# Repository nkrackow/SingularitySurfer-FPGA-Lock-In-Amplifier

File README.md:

# SingularitySurfer: An FPGA Lock-In Amplifier
Repository of an FPGA based DSP Lock-In Amplifier.

## Fotos:

Measuring the change of phase due to changing the distance of two speakers (of which one functions as a crappy microphone):

## Block Diagram:

## Overview:
Lock-In amplifiers are a very useful tool in many physics and bio experiments where your signal of interest might be covered by a lot of noise and interference. It does so by effectively correlating out the signal of interest. As analog components are always subject to noise, drift and non-linearities, performance in a DSP Lock-In can be far superior.
The project leverages the affordable ICE40 FPGA with its fully open source toolchain to implement the digital signal processing. Analog components are implemented in a manner that strikes a balance between performance and cost. As the analog frontend mostly determines the overall performance, a focus was put on its implementation. The total BOM cost is below 70€.
The SingularitySurfer was developed as a personal learning platform that I share so others can get design ideas and see my approach. It does not intend to give reference designs or to teach the subject. 
Cores from other people:
* CORDIC: https://opencores.org/projects/verilog_cordic_core
* SPI flash reader: https://github.com/smunaut/ice40-playground/tree/master/cores/spi_flash
* 2x16 character display driver: https://opencores.org/projects/wb_lcd

The next sections will describe the features of the various sub-systems, their development and the design decisions made.

## Digital architecture:
All of the FPGA cores run at a 36MHz base clock and the numeric oscillator, DDS, PLL and DACs also run at this sample frequency. However the ADC samples at 900kHz and the digital filters further downsample the signal by a factor of 1024. The DDS and the ADC produce signed 16 bit signals, while the output of the multipliers and filters are signed 32 bit. The phase signals from the PLL and oscillator are 18 bit. Due to FPGA LUT constraints, the CORDIC core only uses signed 16bit precision and the algorithm is terminated after 9 iterations. Most of the cores, especially the CORDIC core, make use of pipelining to maintain the 36MHz clock. The full design takes up about 85% of the FPGA LUTs.

## FPGA:
The Lattice ICE40UP5K is an ideal platform for a small DSP project like this. It offers:
* sufficient LUTs for all of the wiring, UI, display and housekeeping
* 8 16x16 hardware multipliers for signal processing
* 1Mbit of internal SRAM for storing a high fidelity sine lookup table
* QFP package which is easily soldered by hand
* affordable price at just 5€
* fully open source toolchain!

## Analog frontend:
As all of the digital signal processing is deterministic and can be upgraded at a later point, the Lock-In’s performance is ultimately determined by the analog frontend. The goal is to transfer the signal into the digital domain with little disturbance. This requires high dynamic range, low noise and high linearity. But as cost was also a factor in the development, compromises had to be made. The design employs:
* ADC: MCP33131D, 1MSps, 16bit, 91.3dB SNR 
* Voltage reference: REF5050, low noise, low drift
* PGA: AD8253, 0-60dB gain, low distortion, low noise, instrumentation amplifier
* OpAmp: AD8675, low noise
* Voltage regulator: LT3032-15, dual +-15V, low noise

At the input there is a 100kHz RC lowpass and the ADC AA filter is tuned to 100kHz as well. The PGA doubles as the ADC driver, using the AD8675 to make the signal differential. This setup was used to cut the cost of a dedicated ADC driver. Unfortunately it does limit performance, as it does introduce some distortion due to the PGA output not being fast enough to drive the ADC (which is not critical as distortion is essentially the same as noise well outside the passband of the digital lowpass). Broadband noise from the analog components was below the quantization noise and therefore not visible at the ADC output.

## DDS and numeric oscillator:
The direct digital synthesis core generates a digital representation of a sinusoidal using a 1/4 sinus look-up table stored in the 1Mbit SRAM. The other 3/4 of the sine and the cosine can be easily generated from the first 1/4 using symmetries. Therefore a high fidelity, 16bit amplitude, 18bit phase representation of the sinusoidals can be generated. When using an external reference signal, the DDS uses the phase of the digital PLL locked to the external reference signal. When generating its own reference signal, a numeric oscillator with an internal 32bit phase accumulator is employed. 
In order to avoid spurious tones in the output spectrum of the DDS when using the internal oscillator, dithering of the last phase-bit is applied using a linear-feedback shift register. Unfortunately the ICE40 SRAM blocks don't support initial values in the FPGA bitstream. Therefore the look-up table is permanently stored in the external SPI flash and loaded into SRAM after every startup.

## DAC:
As the Lock-In’s performance is not dependent on the output reference signal (as long as it contains a strong spectral component exactly at the reference frequency and other spectral components are masked by the noise added in the DUT), a basic sigma-delta DAC is used. Same goes for the X/R and Y/Theta "baseband" outputs, as they are essentially just DC (however DC accuracy has to be considered here) . The sigma-delta DACs require just a single FPGA pin and a passive second order lowpass with buffered output as external hardware in order to generate analog signals. Inside the FPGA the DAC uses a basic first-order sigma-delta modulator. With a modulator frequency of 36 MHz and 100kHz lowpass cutoff, the SNR is still better than 60dB. However switching many single-ended FPGA pins at these frequencies might lead to high EMI emissions. This was tried to be avoided by placing the lowpass filter close to the FPGA pins.

## PLL *(experimental)*:
The all-digital PLL gets a clean digital input signal by the use of a Schmitt-Trigger at the reference input. It uses a 32bit phase accumulator and 17bit phase increment word which leads to good phase precision. The DP controller can update the phase increment word without the need for multipliers by simply bit shifting the error signals. The controller can therefore only be tuned very coarsely which was done by simple trial and error. With this setup the controller can lock and track any reference signal between 500Hz and 100kHz. However it can get stuck in "limbo" with an aperiodic input signal and needs a reset to recover.

## Multipliers and CIC filter:
Twor 16x16 hardware multipliers directly "mix" the incoming ADC samples with the sine/cosine signals from the DDS core. The output is therefore a 32bit signal at ADC sampling speed. 
This signal needs to be lowpass filtered to get rid of the undesired mixing products, ideally with a very low cutoff frequency (i.e. long time-constant). At ADC sampling speed this would require a lot of memory. But as the desired signal is bandlimited to a very low frequency (10s or 100s of Hz), a high sampling rate is unnecessary. A cascaded integrator comb (CIC) filter can downsample and lowpass filter the signal at the same time. Furthermore the cutoff frequency can easily be changed in powers of two and it doesn’t require hardware multipliers. 
The downside is that the frequency response is far from an ideal lowpass. Fortunately in the case of the lock-in, this is not critical, as the cutoff frequencies are so low and the upper mixer output products are far higher than fc (it will just let more noise through which can be counteracted by a longer filter time constant). In fact right now, only a single IC stage is used in the SingularitySurfer, as there is already not enough memory for a second integrator. A good improvement would be to follow the CIC with an IIR filter using the remaining hardware multipliers.

## *(update 2020)* Multiplier less IIR filter
The SingularitySurfer was recently upgraded with a better lowpass using a very clever first order IIR filter. It uses the fact that you can multiply by a number close to 1 with bitshifting in hardware. E.g x*(15/16) can be accomplished via x-(x>>4). See [PYTHON_FILTER](https://github.com/SingularitySurfer/SingularitySurfer-FPGA-Lock-In-Amplifier/tree/master/PYTHON_FILTER) for a python demonstration.

## CORDIC:
The CORDIC algorithm computes the angle and magnitude of the sine and cosine signals. The original core by Dale Dickard was extended to support full 360 degree rotation and modified to fit into the remaining ICE40 logic. 

## Display and UI:
The display allows direct monitoring of the Lock-In outputs and user interaction with the UI. The UI is controlled via four buttons on the side of the display. This way the user can navigate through the device settings:
* Filter time constant: between 2^0 and 2^15 milliseconds
* PGA gain: 0dB, 20dB, 40dB, 60dB
* Internal/external reference 
* Internal reference frequency: 500Hz, 1kHz, 2kHz, 5kHz, 10kHz, 20kHz, 50 kHz, 100kHz
*  Internal reference output amplitude: 0.45V, 0.9V, 1.6V, 3.3V (peak to peak)

The signal monitoring can easily be switched between X/Y and R/θ view. The display is a simple 2x16 character LCD display with built-in character ROM. Unfortunately, the maximum update rate of such a display is about 2Hz. A higher update rate would lead to a more direct user feedback when monitoring signals. The logic to drive the display, show text, decimal numbers, etc., is actually not trivial and a small embedded processor could be a better idea in a future project.

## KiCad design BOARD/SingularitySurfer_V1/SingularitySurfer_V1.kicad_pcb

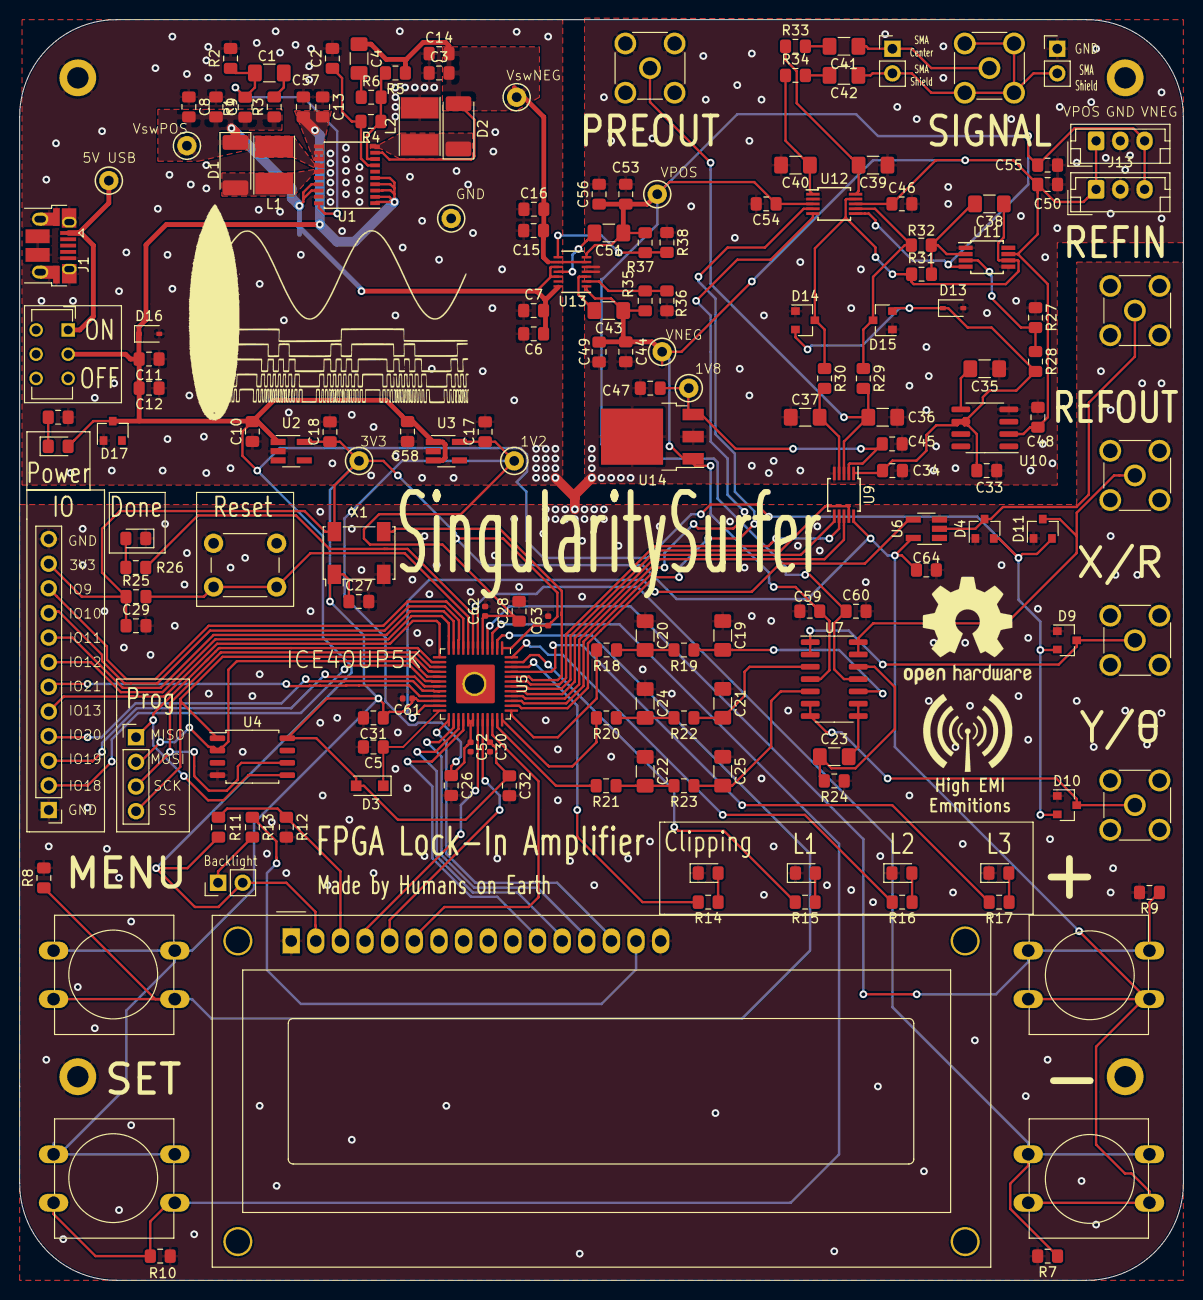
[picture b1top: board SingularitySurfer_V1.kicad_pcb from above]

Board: 2 copper layers, 120.0 x 130.0 mm, 171 parts (0 on the bottom side), 99 nets.

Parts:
 : TestPoint; TestPoint_Keystone_5000-5004_Miniature
 #2,  #3,  #4,  #5: MountingHole_2.2mm_M2_DIN965_Pad
 #6: Conn_01x02_Male; PinHeader_1x02_P2.54mm_Vertical
 #7: Conn_01x12; PinHeader_1x12_P2.54mm_Vertical
 #8: Conn_01x04_Male; PinHeader_1x04_P2.54mm_Vertical
 #9,  #12,  #13,  #14,  #15,  #16,  #17,  #18: TestPoint; TestPoint_Keystone_5000-5004_Miniature
 #10: R; R_0805_2012Metric_Pad1.15x1.40mm_HandSolder
 #11: Conn_01x03; JST_EH_B3B-EH-A_1x03_P2.50mm_Vertical
 #19,  #20,  #21,  #22,  #23,  #24: LED; LED_0805_2012Metric_Pad1.15x1.40mm_HandSolder
 #25,  #27,  #30,  #31,  #32,  #33: Conn_Coaxial; SMA_Molex_73251-2200_Horizontal
 #26: SW_Push; SW_PUSH_6mm
 #28,  #29: Conn_01x02; PinHeader_1x02_P2.54mm_Vertical
 #34: WC1602A
 #35: SW_DIP_x01; SW_CuK_JS202011AQN_DPDT_Angled
+1: SW_Push; SW_PUSH-12mm
-1: SW_Push; SW_PUSH-12mm
C1, C4, C19, C20, C21, C22, C23, C24, C25, C36, C37, C38, C39, C40, C41, C42, C43, C51: C; C_1206_3216Metric_Pad1.42x1.75mm_HandSolder
C2, C3, C5, C6, C7, C8, C9, C10, C11, C12, C13, C14, C15, C16, C17, C18, C26, C27, C28, C29, C31, C32, C44, C45, C46, C47, C48, C49, C50, C53, C54, C55, C56, C57, C58, C59, C60, C64: C; C_0805_2012Metric_Pad1.15x1.40mm_HandSolder
C30, C52, C61, C62, C63: C; C_0402_1005Metric
C33, C34: 10u; C_0805_2012Metric_Pad1.15x1.40mm_HandSolder
C35: 1u; C_1206_3216Metric_Pad1.42x1.75mm_HandSolder
D1, D2: D; D_2010_5025Metric_Pad1.52x2.65mm_HandSolder
D3: D; D_SOD-123F
D4, D9, D10, D11, D14, D15, D17: D_Schottky_x2_Serial_AKC; SOT-23
D13, D16: D_Zener; D_SOD-323
J1: USB_B_Micro; USB_Micro-B_Amphenol_10103594-0001LF_Horizontal
J13: Conn_01x03; JST_EH_B3B-EH-A_1x03_P2.50mm_Vertical
L1, L2: INDUCTOR; L_Taiyo-Yuden_NR-40xx_HandSoldering
MENU1: SW_Push; SW_PUSH-12mm
R1, R2, R3, R4, R5, R6, R7, R8, R9, R10, R11, R12, R13, R14, R15, R16, R17, R18, R19, R20, R21, R22, R23, R24, R25, R26, R27, R28, R29, R30, R31, R32, R33, R34, R35, R36, R37, R38: R; R_0805_2012Metric_Pad1.15x1.40mm_HandSolder
SET1: SW_Push; SW_PUSH-12mm
U1: BD81870EFV; SSOP-20_4.4x6.5mm_P0.65mm
U2: MIC5504-3.3YM5; SOT-23-5_HandSoldering
U3: TLV70212_SOT23-5; SOT-23-5_HandSoldering
U4: W25Q32JVSS; SOIC-8_5.23x5.23mm_P1.27mm
U5: ICE40UP5K-SG48ITR; QFN-48-1EP_7x7mm_P0.5mm_EP5.6x5.6mm
U6: 74LVC1G17; SOT-23-5_HandSoldering
U7: OPA1679; SOIC-14_3.9x8.7mm_P1.27mm
U9: MCP33131D; MSOP-10_3x3mm_P0.5mm
U10: REF5050AD; SOIC-8_3.9x4.9mm_P1.27mm
U11: AD8675; MSOP-8_3x3mm_P0.65mm
U12: AD8253; MSOP-10_3x3mm_P0.5mm
U13: LT3032; DFN-14-1EP_split_bottom_pad_3x4mm_P0.5mm_EP1.7x3.3mm
U14: AP2114-1.8; TO-252-3_TabPin2
X1: DFA-S11; Oscillator_SMD_Fordahl_DFAS11-4Pin_7.0x5.0mm

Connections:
1V2: #12.1, C17.1, C26.1, C28.1, C52.1, C62.1, U3.5, U5.5, U5.29, U5.30
1V8: #16.1, C45.1, C47.1, U9.2, U14.3
3V3: #7.11, #9.1, +1.2, -1.2, C18.1, C27.1, C29.1, C30.1, C31.1, C32.1, C61.1, C63.1, C64.1, D3.2, MENU1.2, R25.1, SET1.2, U2.5, U4.8, U5.1, U5.22, U5.33, U6.5, U9.10, X1.1, X1.4
5V: #6.2, #19.2, #34.2, #35.2, C10.2, C11.2, C12.2, C13.2, C57.2, C58.2, D4.2, D9.2, D10.2, D11.2, D16.1, D17.3, R11.1, U1.1, U1.2, U1.3, U1.4, U1.5, U1.11, U1.12, U1.13, U2.1, U3.1, U3.3
+8V: #11.1, #15.1, C43.1, C44.1, C46.1, C48.1, C49.1, C50.1, C59.1, J13.1, R35.2, U7.4, U10.2, U11.7, U12.8, U13.1, U14.1
-8V: #11.3, #13.1, C51.1, C53.1, C54.1, C55.1, C56.1, C60.1, J13.3, R37.2, U7.11, U11.4, U12.3, U12.6, U13.7
/Power/VNEG: #14.1, C3.2, C4.1, C14.2, C15.2, C16.2, D2.2, R5.1, U1.9, U13.6, U13.9
A0: U5.38, U12.4
A1: U5.39, U12.5
CDONE: R26.2, U5.7
CONVST: U5.41, U9.6
GND: .1, #2.1, #3.1, #4.1, #5.1, #7.1, #7.12, #10.1, #11.2, #20.1, #21.1, #22.1, #23.1, #24.1, #25.2, #26.1, #28.1, #30.2, #31.2, #32.2, #33.2, #34.1, #34.16, C2.2, C3.1, C5.2, C6.1, C7.1, C8.1, C9.1, C10.1, C11.1, C12.1, C13.1, C14.1, C15.1, C16.1, C17.2, C18.2, C19.1, C20.1, C21.1, C22.1, C24.1, C25.1, C26.2, C27.2, C28.2, C29.2, C30.2, C31.2, C32.2, C33.2, C34.2, C35.1, C36.1, C37.1, C39.1, C40.2, C44.2, C45.2, C46.2, C47.2, C48.2, C49.2, C50.2, C52.2, C53.2, C54.2, C55.2, C56.2, C57.1, C58.1, C59.2, C60.2, C61.2, C62.2, C63.2, C64.2, D4.1, D9.1, D10.1, D11.1, D13.2, D14.1, D15.1, D16.2, D17.1, J1.5, J1.6, J13.2, L2.2, R2.2, R7.2, R8.2, R9.2, R10.2, R12.2, R24.1, R27.1, R36.1, R38.1, U1.16, U1.19, U2.2, U3.2, U4.4, U5.49, U6.3, U9.5, U10.4, U11.1, U11.5, U12.2, U13.4, U13.5, U14.2, X1.2
unnamed: +1.1, R9.1, U5.4
unnamed: -1.1, R7.1, U5.6
unnamed: C1.1, R3.2
unnamed: C1.2, R1.2, R2.1, U1.20
unnamed: C2.1, R4.2, U1.7
unnamed: C4.2, R6.1
unnamed: C5.1, D3.1, U5.24
unnamed: C19.2, R19.1, U7.10
unnamed: C20.2, R18.1, R19.2
unnamed: C21.2, R22.1, U7.3
unnamed: C22.2, R21.1, R23.2
unnamed: C23.1, R24.2, U7.12
unnamed: C23.2, U7.8, U7.9
unnamed: C24.2, R20.1, R22.2
unnamed: C25.2, R23.1, U7.5
unnamed: C33.1, C34.1, D13.1, D14.2, D15.2, R28.2, U9.1, U10.6
unnamed: C35.2, U10.5
unnamed: #25.1, C36.2, R29.2, U9.3
unnamed: C37.2, R30.2, U9.4
unnamed: C38.1, D14.3, R30.1, R31.1, U11.6, U12.9
unnamed: C38.2, R31.2, R32.2, U11.2
unnamed: C39.2, R33.1, U12.10
unnamed: C40.1, R34.1, U12.1
unnamed: #27.1, #29.1, C41.1
unnamed: C41.2, R33.2
unnamed: #27.2, #28.2, #29.2, C42.1
unnamed: C42.2, R34.2
unnamed: C43.2, U13.3
unnamed: C51.2, U13.11
unnamed: D1.2, L1.1, U1.15
unnamed: D2.1, L2.1, U1.10
unnamed: #33.1, D4.3, U6.2
unnamed: #24.2, R14.1
unnamed: #23.2, R15.1
unnamed: #22.2, R16.1
unnamed: #21.2, R17.1
unnamed: #31.1, D9.3, U7.1, U7.2
unnamed: #30.1, D10.3, U7.6, U7.7
unnamed: #32.1, D11.3, U7.13, U7.14
unnamed: #20.2, R26.1
unnamed: D15.3, R29.1, R32.1, U12.7
unnamed: #10.2, #19.1
unnamed: #34.3, R11.2, R12.1
unnamed: #34.4, U5.31
unnamed: #34.5, U5.32
unnamed: #34.6, U5.34
unnamed: #34.11, U5.28
unnamed: #34.12, U5.27
unnamed: #34.13, U5.26
unnamed: #34.14, U5.25
unnamed: #34.15, R13.1
unnamed: #17.1, #35.1, J1.1
unnamed: #8.1, U4.5, U5.14
unnamed: #8.2, U4.2, U5.17
unnamed: #8.3, U4.6, U5.15
unnamed: #8.4, U4.1, U5.16
unnamed: #7.2, U5.18
unnamed: #7.3, U5.19
unnamed: #7.4, U5.20
unnamed: #7.5, U5.13
unnamed: #7.6, U5.21
unnamed: #7.7, U5.12
unnamed: #7.8, U5.11
unnamed: #7.9, U5.10
unnamed: #7.10, U5.9
unnamed: #6.1, R13.2
unnamed: L1.2, U1.14
unnamed: MENU1.1, R8.1, U5.2
unnamed: R4.1, R5.2, R6.2, U1.8
unnamed: R10.1, SET1.1, U5.3
unnamed: R14.2, U5.46
unnamed: R15.2, U5.47
unnamed: R16.2, U5.48
unnamed: R17.2, U5.45
unnamed: R18.2, U5.37
unnamed: R20.2, U5.36
unnamed: R21.2, U5.35
unnamed: R27.2, R28.1, U11.3
unnamed: R35.1, R36.2, U13.2
unnamed: R37.1, R38.2, U13.8
unnamed: U5.23, U6.4
unnamed: U5.44, X1.3
SCLK: U5.40, U9.8
SDI: U5.42, U9.9
SDO: U5.43, U9.7
VPOS: #18.1, C6.2, C7.2, C8.2, C9.2, D1.1, R1.1, R3.1, U1.17, U1.18, U13.10, U13.12, U13.14
nCRESET: #26.2, R25.2, U5.8

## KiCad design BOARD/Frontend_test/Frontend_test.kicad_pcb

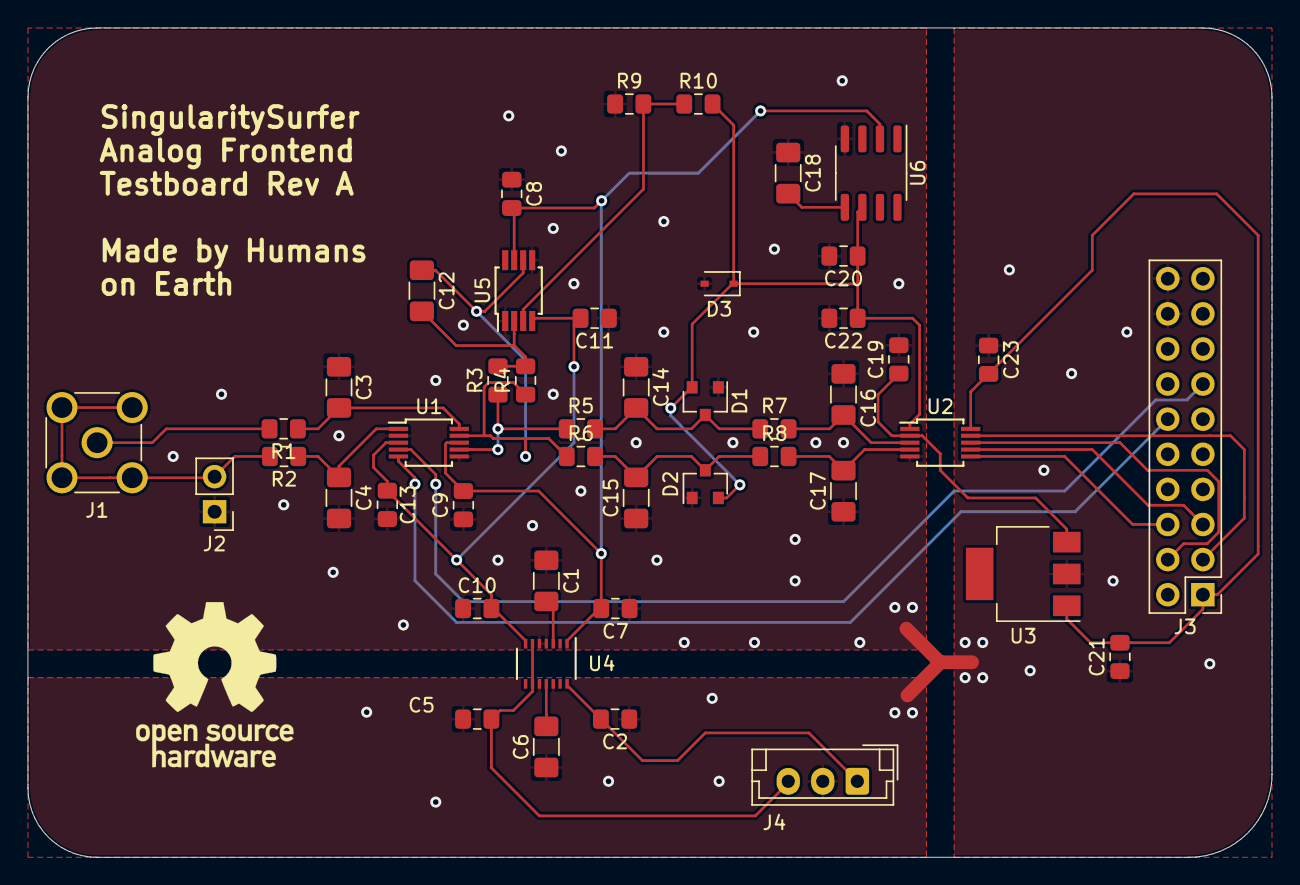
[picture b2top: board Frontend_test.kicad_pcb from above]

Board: 2 copper layers, 90.0 x 60.0 mm, 46 parts (0 on the bottom side), 29 nets.

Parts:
C1, C6: 10n; C_1206_3216Metric_Pad1.42x1.75mm_HandSolder
C2, C5, C7, C8, C9, C10, C11, C13, C19, C20, C21, C22, C23: 10u; C_0805_2012Metric_Pad1.15x1.40mm_HandSolder
C3, C4, C12, C14, C15, C16, C17: C; C_1206_3216Metric_Pad1.42x1.75mm_HandSolder
C18: 1u; C_1206_3216Metric_Pad1.42x1.75mm_HandSolder
D1, D2: D_Schottky_x2_Serial_AKC; SOT-23
D3: D_Zener; D_SOD-323
J1: Conn_Coaxial; SMA_Molex_73251-2200_Horizontal
J2: Conn_01x02; PinHeader_1x02_P2.54mm_Vertical
J3: Conn_02x10_Top_Bottom; PinHeader_2x10_P2.54mm_Vertical
J4: Conn_01x03; JST_EH_B3B-EH-A_1x03_P2.50mm_Vertical
R1, R2, R3, R4, R5, R6, R7, R8, R9, R10: R; R_0805_2012Metric_Pad1.15x1.40mm_HandSolder
U1: AD8253; MSOP-10_3x3mm_P0.5mm
U2: MCP33131D; MSOP-10_3x3mm_P0.5mm
U3: AP2114-1.8; SOT-223
U4: LT3032-15; DFN-14-1EP_split_bottom_pad_3x4mm_P0.5mm_EP1.7x3.3mm
U5: AD8675; MSOP-8_3x3mm_P0.65mm
U6: REF5050AD; SOIC-8_3.9x4.9mm_P1.27mm

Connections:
+15V: C7.2, C8.2, C9.2, U1.8, U4.1, U5.7, U6.2
-15V: C10.2, C11.2, C13.2, U1.3, U4.7, U5.4
/+3.3V: C21.2, C23.2, J3.1, U2.10, U3.1
A0: J3.13, U1.4
A1: J3.12, U1.5
DGND: C1.1, C2.1, C3.1, C4.2, C5.2, C6.1, C7.1, C8.1, C9.1, C10.1, C11.1, C13.1, C14.1, C15.1, C16.1, C17.1, C18.1, C19.2, C20.2, C21.1, C22.2, C23.1, D1.1, D2.1, D3.2, J2.1, J3.18, J3.20, J4.2, R9.1, U1.2, U1.6, U2.5, U3.2, U4.4, U4.5, U4.10, U4.12, U5.1, U5.5, U6.4
unnamed: C1.2, U4.3
unnamed: C2.2, J4.1, U4.14
unnamed: C3.2, R1.1, U1.10
unnamed: C4.1, R2.1, U1.1
unnamed: C5.1, J4.3, U4.6, U4.9
unnamed: C6.2, U4.11
unnamed: C12.1, R4.1, R6.1, U1.9, U5.6
unnamed: C12.2, R3.2, R4.2, U5.2
unnamed: C14.2, D1.3, R5.2, R7.1
unnamed: C15.2, D2.3, R6.2, R8.1
unnamed: C16.2, R7.2, U2.3
unnamed: C17.2, R8.2, U2.4
unnamed: C18.2, U6.5
unnamed: C19.1, U2.2, U3.3
unnamed: C20.1, C22.1, D1.2, D2.2, D3.1, R10.2, U2.1, U6.6
unnamed: J1.1, R1.2
unnamed: J1.2, J2.2, R2.2
unnamed: J3.3, U2.9
unnamed: J3.4, U2.8
unnamed: J3.5, U2.7
unnamed: J3.6, U2.6
unnamed: R3.1, R5.1, U1.7
unnamed: R9.2, R10.1, U5.3

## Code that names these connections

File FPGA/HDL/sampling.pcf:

set_io CLK12 37   # Bridged from pin 35!!! pnr fails with 35 as input to PLL


# RGB LED
set_io R 41
set_io G 40
set_io B 39

# Header C outside +v inside

set_io sMISO 47
set_io sMOSI 44
set_io sSCLK 46
set_io sCS 2



# ADC interfaces

set_io SDI 23         #37A
set_io SCLK 26        #39A
set_io SDO 25         #36B
set_io CONVST 36      #48B
set_io GAIN_A1 38     #50B
set_io GAIN_A0 31     #42B



# Switches
set_io S[0] 43
set_io S[1] 34

# SPI flash
set_io ss   16
set_io miso 17
set_io mosi 14
set_io sck  15

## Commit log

2019-08-29 Initial commit. DDS with 1/4 sine lookup in SRAM fully working. SRAM initialization from SPI Flash working. Sigma-Delta fully working at 30MHz. Signed multiplier working :)
2019-09-02 implemented PLL with proportional and derivative loopfilter with gain set by dividing the error terms.
2019-09-09 Analog Frontend Testboard designed and out in Production :)
2019-09-21 finished the analog frontend testboard and the fpga sampling hardware. The FPGA samples into the internal SRAM and then transfers the data via serial to the analog discovery. the AD is scripted to re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
2019-09-24 Power Supply Section of final Board done
2019-09-26 More work on final Schematic. Power, digital and output section close to final. No frontend yet.
2019-09-29 Final Board schematic almost done and started on layout
2019-10-03 SignularitiSurfer final boar almost donegit status! Fuuuak this is getting rediculous...
2019-10-05 Final board done, plotted and in production. Started on LCD driver, already working with scrolling HI :)
2019-10-07 Lots of work on the UI with 1602LCD and Buttons. Binary to LCD driver coded output fully working. Menu States not fully done yet.
2019-10-08 UI basically done, only need to add the different values for timeconstatnt etc.
2019-10-09 Pipelined BinToLCD output. CORDIC Core in Pipelined mode changed from generate loop to just lots of code. FUCKING R/Thet output not working -.-
2019-10-09 Implemented integrator comb. Unfortunately no cascade yet cuz integrators get HUUUGE :/
2019-10-14 Board fully assembled over the course of like 50 hours... SO much PAIIIN.. BUT IT FUCKING WOOOORKS :) wrote some testcode for buttons and leds. frontend testing next!
2019-10-18 lots of work on various topics. Lots of board and filter testing, dds on the SS board and now working on CORDIC but not working yet due to timing..
2019-10-21 lots of final work like PLL integrated, UI implementation, tweaks etc. Filter not working with big Ratechange yet...
2020-03-13 Add files via upload
    fotos
2020-03-13 Add files via upload
    bock diagram
2020-03-13 finally updated readme
2020-03-13 readme fixes
2020-03-13 NOT chill down...
2020-06-12 idiot me forgot to push final changes half a year ago.. Fixed code: filter constant 3 bit, filter downsampling factor and some mics. Converted KiCad stuff to new version
2020-06-13 python script for multiplier-less IIR filter
2020-06-16 added RIIR filter in migen. gets converted to verilog by makefile and integrated in the top module. also some more minor tweaks.
2020-06-16 fixed idiot sampling spi transfer to analog discovery
2020-06-23 fixed TC, no refout if on external, fixed glitchy lcd nuber out (in an inefficient way)
2023-05-11 small corrections
